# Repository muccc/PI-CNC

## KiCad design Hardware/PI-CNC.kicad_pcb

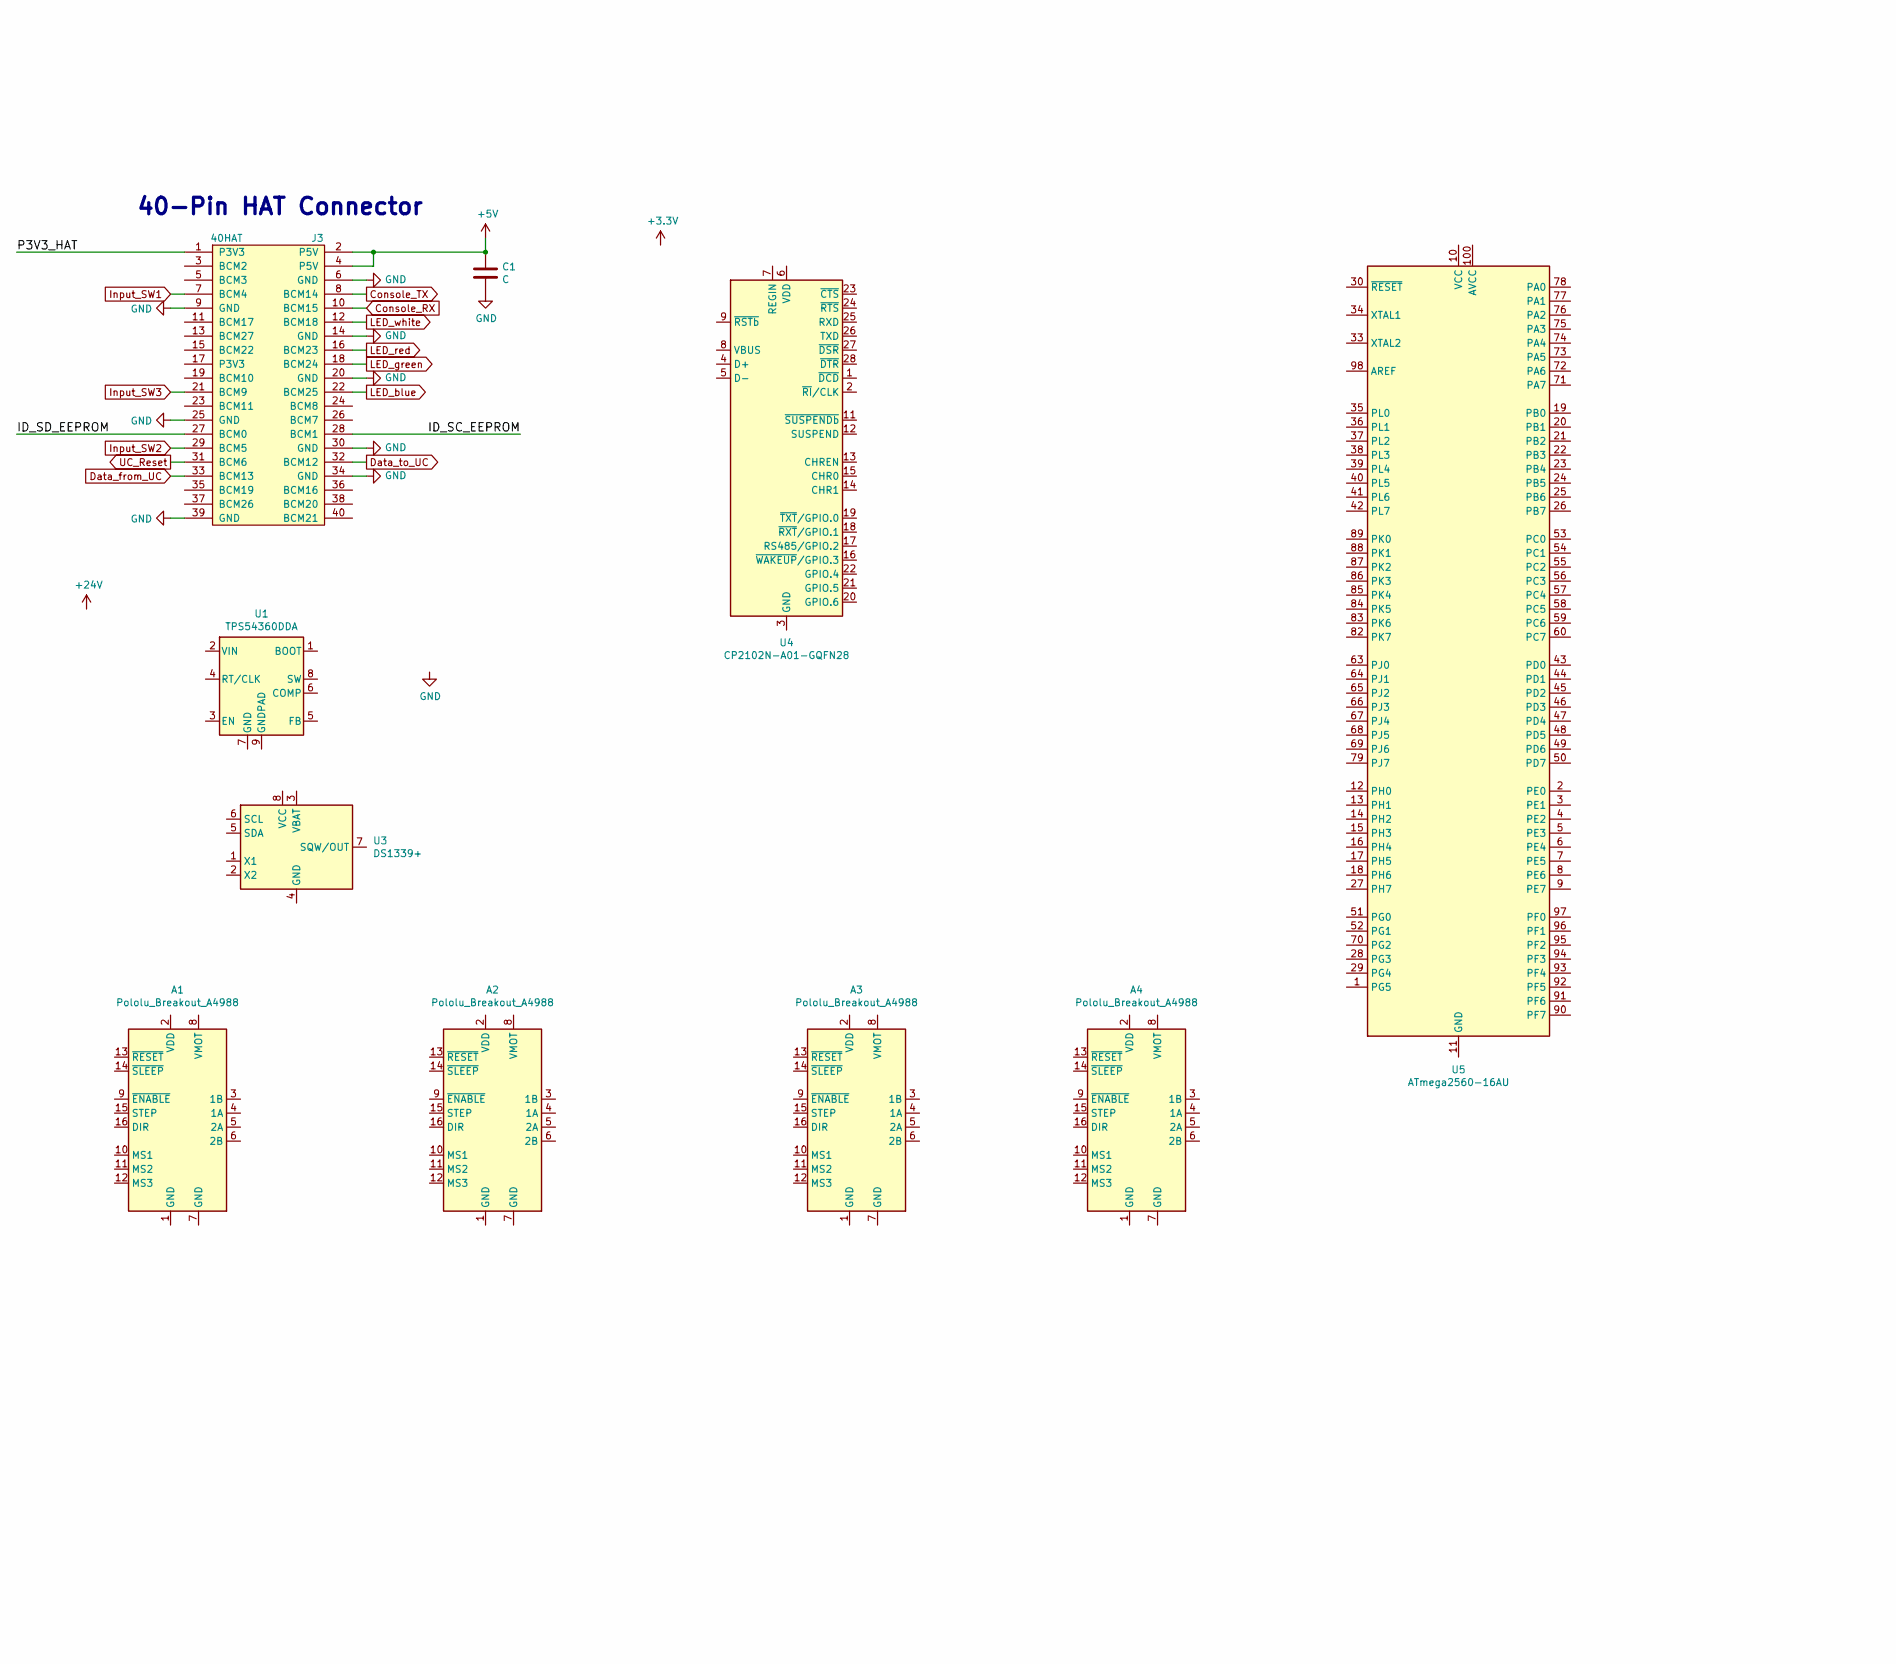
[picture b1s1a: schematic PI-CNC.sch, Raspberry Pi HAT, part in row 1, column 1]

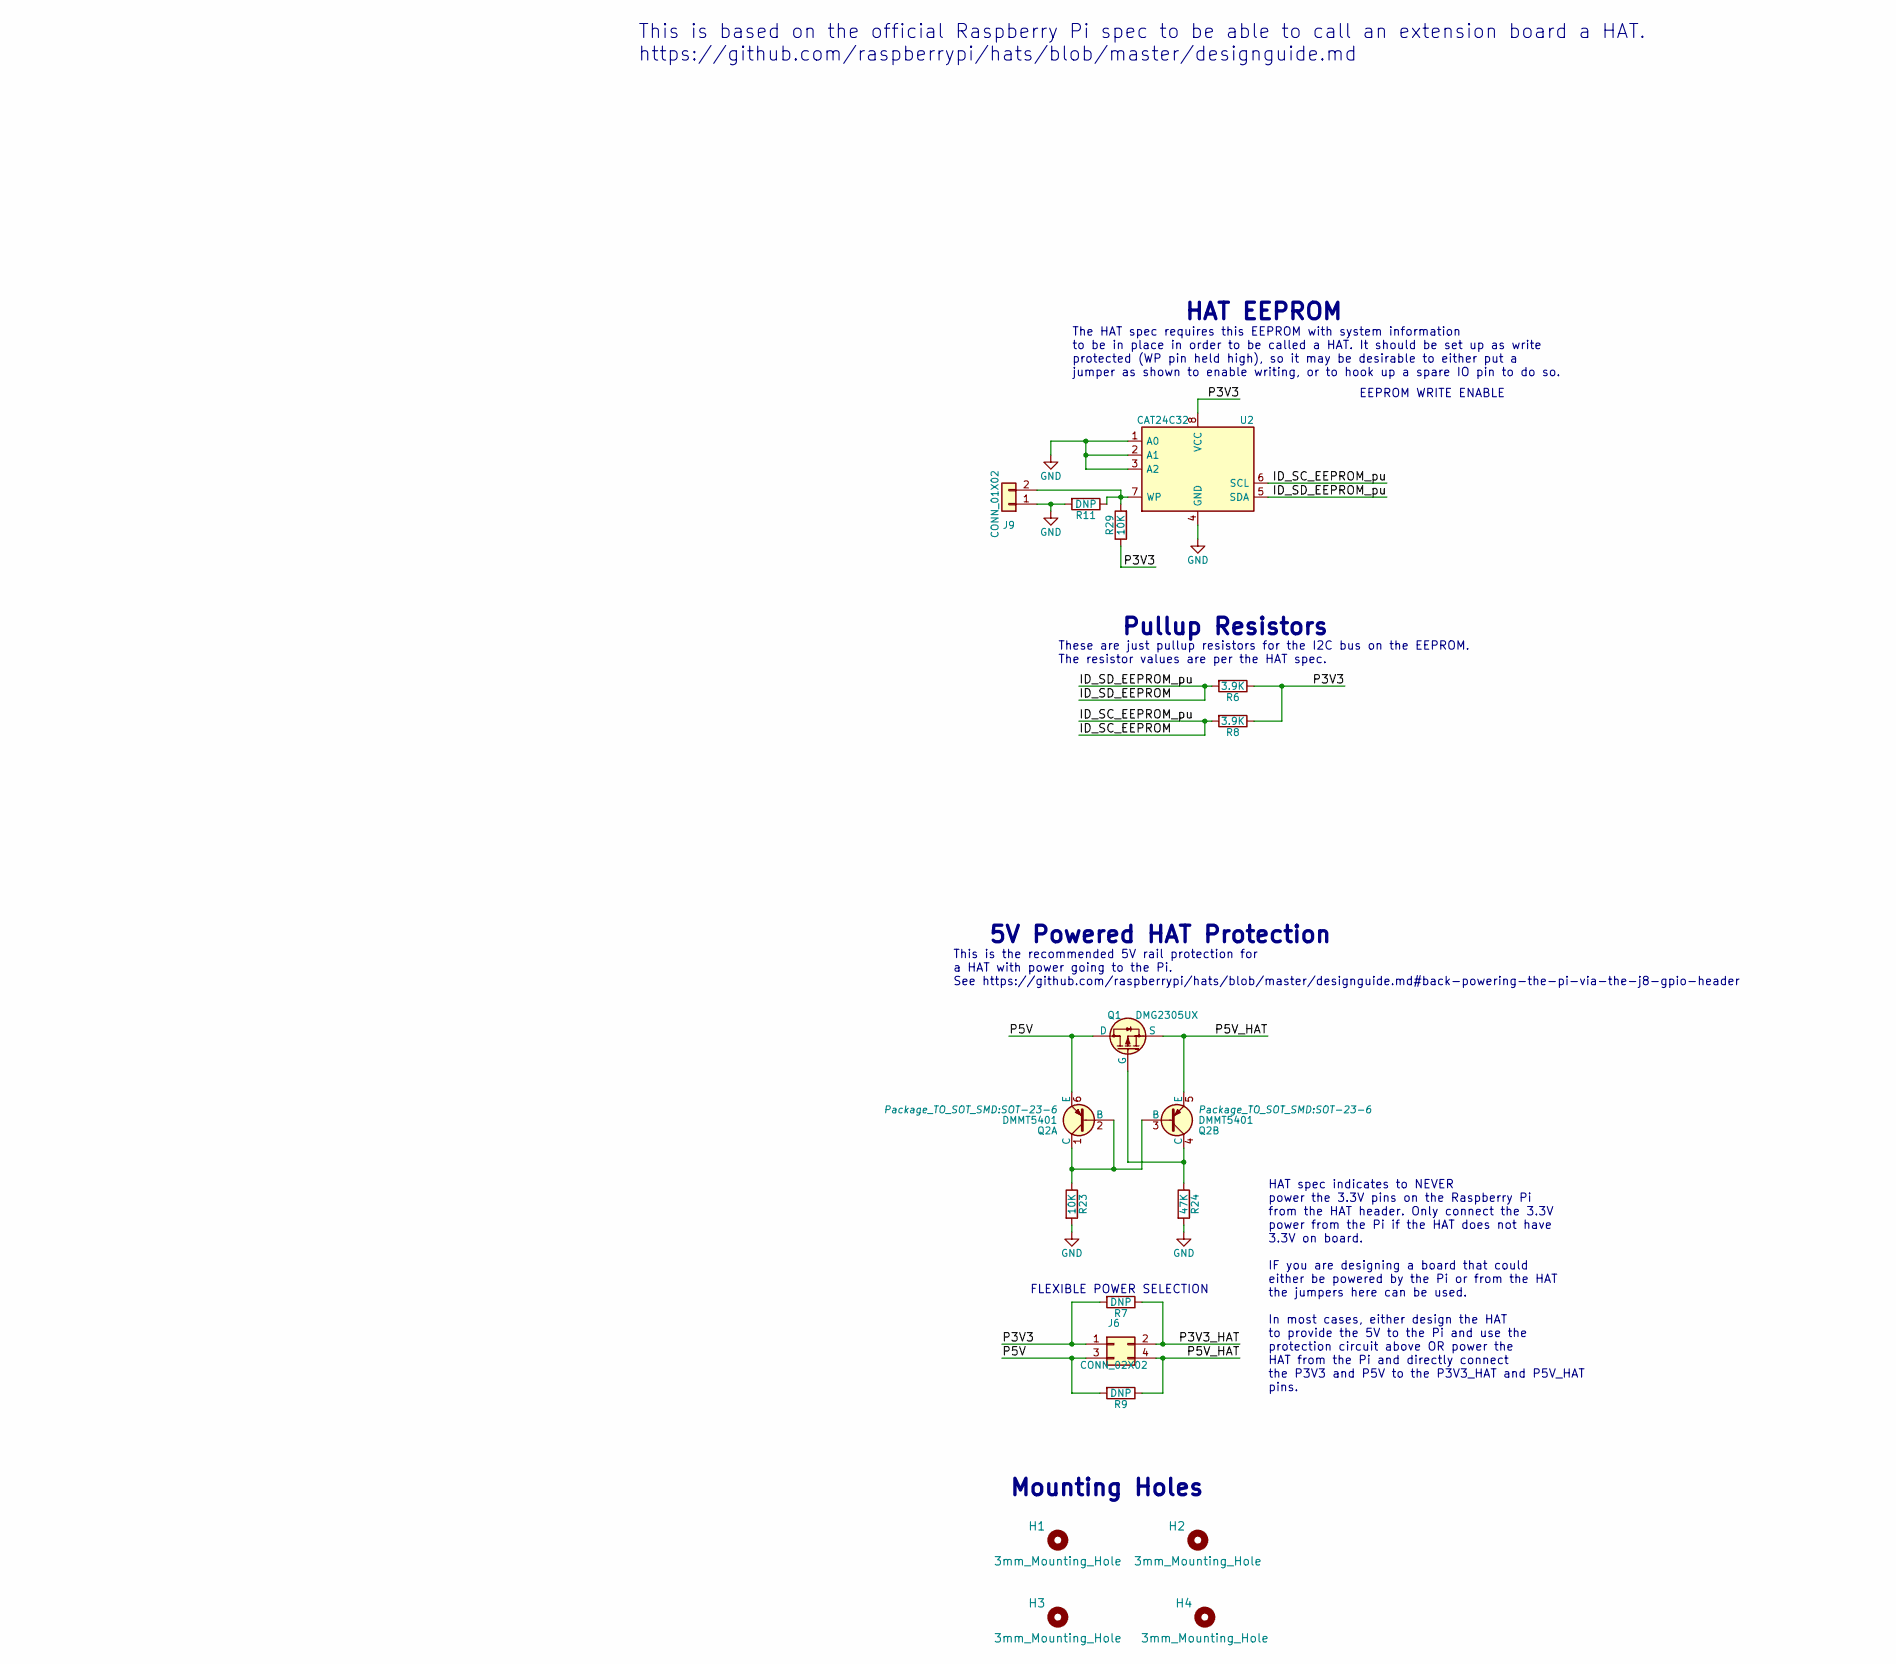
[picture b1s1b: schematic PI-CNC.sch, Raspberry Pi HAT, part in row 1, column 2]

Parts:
A1, A2, A3, A4: Pololu_Breakout_A4988; Pololu_Breakout-16_15.2x20.3mm
C1: C; C_1210_3225Metric
H1, H2, H3, H4: 3mm_Mounting_Hole; NPTH_3mm_ID
J3: 40HAT; PinSocket_2x20_P2.54mm_Vertical
J6: CONN_02X02; PinHeader_2x02_P2.54mm_Vertical
J9: CONN_01X02; PinHeader_1x02_P2.54mm_Vertical
Q1: DMG2305UX; SOT-23
Q2: DMMT5401; SOT-23-6
R6, R8: 3.9K; R_0603_1608Metric_Pad0.84x1.00mm_HandSolder
R7, R9, R11: DNP; R_0603_1608Metric_Pad0.84x1.00mm_HandSolder
R23, R29: 10K; R_0603_1608Metric_Pad0.84x1.00mm_HandSolder
R24: 47K; R_0603_1608Metric_Pad0.84x1.00mm_HandSolder
U1: TPS54360DDA; TI_SO-PowerPAD-8_ThermalVias
U2: CAT24C32; SOIC-8_3.9x4.9mm_P1.27mm
U3: DS1339+; MSOP-8_3x3mm_P0.65mm
U4: CP2102N-A01-GQFN28; QFN-28-1EP_5x5mm_P0.5mm_EP3.35x3.35mm
U5: ATmega2560-16AU; TQFP-100_14x14mm_P0.5mm

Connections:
+5V: C1.1, J3.2 (P5V), J3.4 (P5V)
/ID_SC_EEPROM: J3.28 (BCM1), R8.2, U2.6 (SCL)
/ID_SD_EEPROM: J3.27 (BCM0), R6.2, U2.5 (SDA)
/P3V3: J6.1, R6.1, R7.2, R8.1, R29.1, U2.8 (VCC)
/P3V3_HAT: J3.1 (P3V3), J6.2, R7.1
/P5V: J6.3, Q1.3 (D), Q2.6 (E), R9.2
/P5V_HAT: J6.4, Q1.2 (S), Q2.5 (E), R9.1
Console_RX: J3.10 (BCM15)
Console_TX: J3.8 (BCM14)
Data_from_UC: J3.33 (BCM13)
Data_to_UC: J3.32 (BCM12)
GND: C1.2, J3.6 (GND), J3.9 (GND), J3.14 (GND), J3.20 (GND), J3.25 (GND), J3.30 (GND), J3.34 (GND), J3.39 (GND), J9.1, R11.2, R23.2, R24.2, U2.1 (A0), U2.2 (A1), U2.3 (A2), U2.4 (GND)
Input_SW1: J3.7 (BCM4)
Input_SW2: J3.29 (BCM5)
Input_SW3: J3.21 (BCM9)
LED_blue: J3.22 (BCM25)
LED_green: J3.18 (BCM24)
LED_red: J3.16 (BCM23)
LED_white: J3.12 (BCM18)
unnamed: J9.2, R11.1, R29.2, U2.7 (WP)
unnamed: Q1.1 (G), Q2.4 (C), R24.1
unnamed: Q2.1 (C), Q2.2 (B), Q2.3 (B), R23.1
unnamed: U4.3 (GND), U4.29 (GND)
unnamed: U5.10 (VCC), U5.31 (VCC), U5.61 (VCC), U5.80 (VCC)
unnamed: U5.11 (GND), U5.32 (GND), U5.62 (GND), U5.81 (GND), U5.99 (GND)
UC_Reset: J3.31 (BCM6)

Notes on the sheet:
FLEXIBLE POWER SELECTION
5V Powered HAT Protection
This is the recommended 5V rail protection for a HAT with power going to the Pi. See https://github.com/raspberrypi/hats/blob/master/designguide.md#back-powering-the-pi-via-the-j8-gpio-header
EEPROM WRITE ENABLE
Pullup Resistors
HAT EEPROM
Mounting Holes
40-Pin HAT Connector
HAT spec indicates to NEVER power the 3.3V pins on the Raspberry Pi from the HAT header. Only connect the 3.3V power from the Pi if the HAT does not have 3.3V on board. IF you are designing a board that could either be powered by the Pi or from the HAT the jumpers here can be used. In most cases, e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
The HAT spec requires this EEPROM with system information to be in place in order to be called a HAT. It should be set up as write protected (WP pin held high), so it may be desirable to either put a jumper as shown to enable writing, or to hook up a spare IO pin to do so.
These are just pullup resistors for the I2C bus on the EEPROM. The resistor values are per the HAT spec.
This is based on the official Raspberry Pi spec to be able to call an extension board a HAT. https://github.com/raspberrypi/hats/blob/master/designguide.md

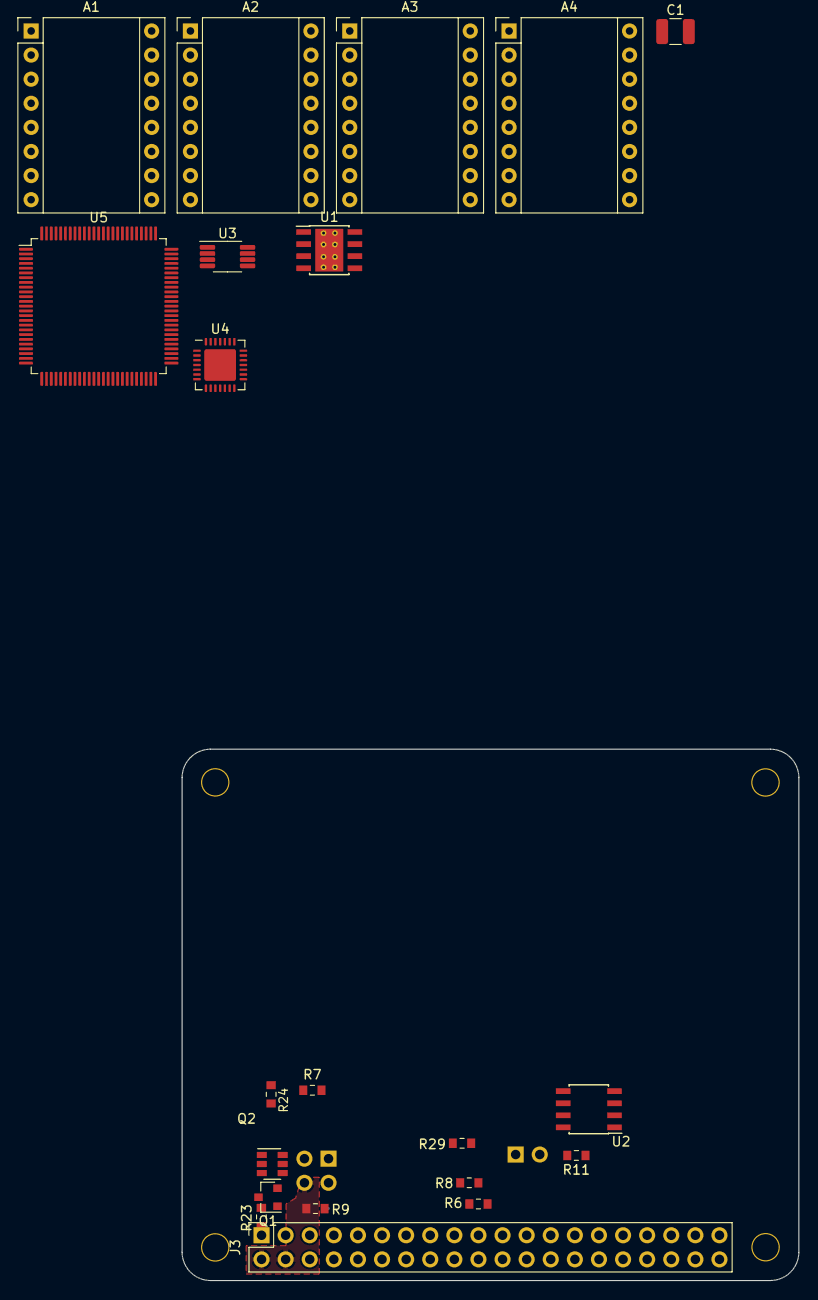
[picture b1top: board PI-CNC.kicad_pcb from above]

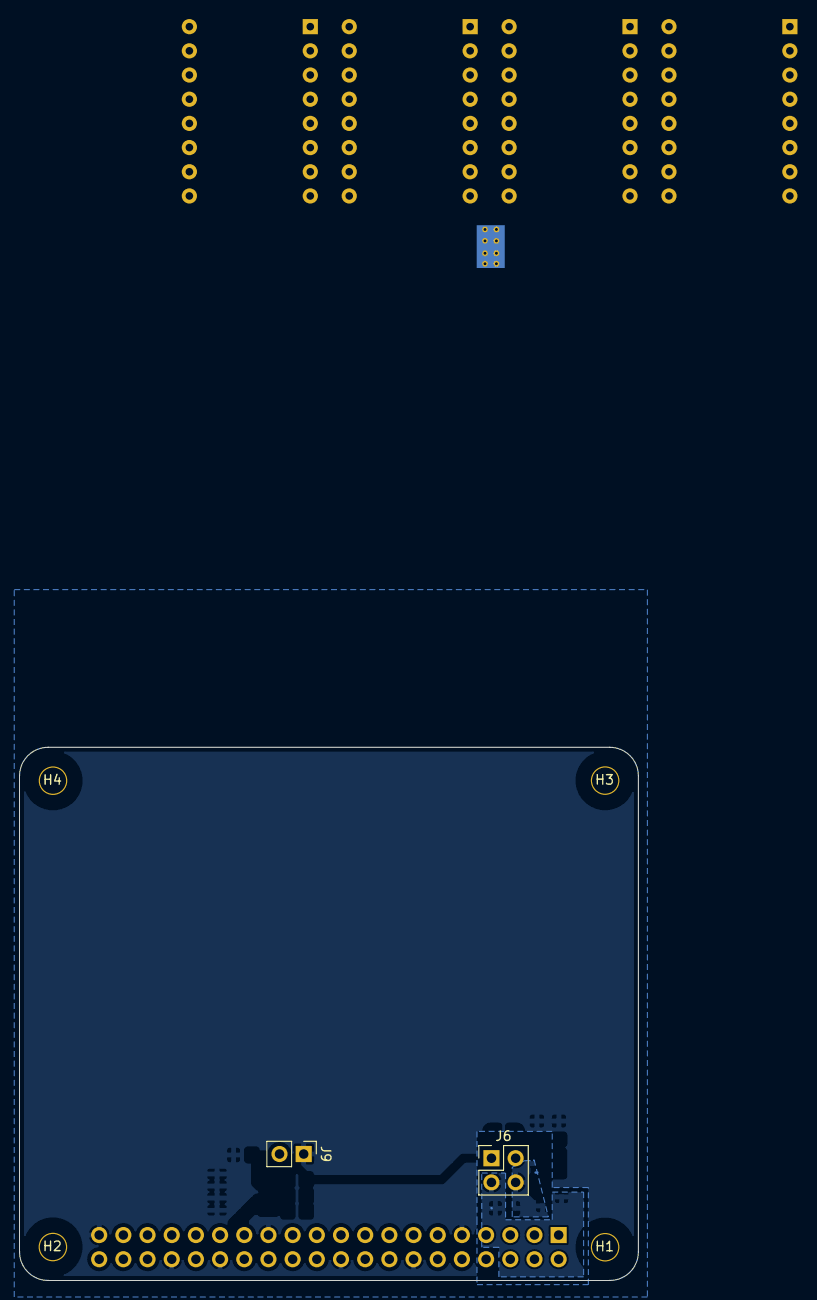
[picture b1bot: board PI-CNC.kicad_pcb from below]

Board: 4 copper layers, 65.0 x 56.0 mm, 27 parts (6 on the bottom side), 14 nets.

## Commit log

2021-01-13 First Hardware Commit, added KiCad Project from PI hat Template and flip PI up.
2021-01-13 add pinout file
2021-01-13 pinout: add ds1339 clock on i2c pins
2021-01-13 Main Parts on schematic and board.
2021-01-13 pinout update
2021-01-13 pinout: place uart1 and ISP
2021-01-23 pinout: add arduino pin mapping
2021-01-24 pinout: add pinmapping endstop / input j20
2021-01-27 pinout: map more pins
